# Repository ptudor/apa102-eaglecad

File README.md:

# apa102 controller

EAGLE schematic and board for apa102 controller

***
## the board

Top:

Bottom:

***

## the schematic

#### Power:

DC 5V, AMS1117-3V3, RT9193GB-33.

There is no onboard 5V voltage regulator. Power is supplied by an external switched power supply at 5V with a 2.1mm center positive jack, in a common wall-wart or laptop brick form factor. Two options are available for providing power: Space for a standard rectangular PCB-mount DC jack exists and optionally, to keep those milled slots clean, two holes labelled "red" and "black" are available for use with circular panel mount DC jacks. A fuse follows the voltage input connectors and a second fuse sits between the regular 5V on the PCB and the 5V supplied to the LED connector. Two big electrolytic capacitors sit after the 5V in and before the MCU side and LED side of the power to hopefully prevent brownouts if a strip suddenly changes from off to fully illuminated.

When connected to external USB, the 5V-USB, after a fuse, powers the onboard atmega88p USBASP and FT230X serial directly and runs to an AMS1117 3.3v voltage regulator that serves the USB Hub, CP2112 i2c, and the USB enable on the uBlox GPS. The 3V3 output has the datasheet suggested 22uF capacitor.

The uBlox GPS is powered by an RT9193 3.3v voltage regulator. The enable pin of this device is connected to the primary MCU on pin D4 so it can be turned off in software. Alternatively, a solder jumper permits connecting the pin directly to the primary 5V. The RT9193 has the datasheet recommended 22nF capacitor on the bypass pin for low-noise operation and the 3V3 output passes though a ferrite bead and tantalum capacitor on its way to the integrated circuit.

#### GPS:

A standard uBlox NEO 7M occupies the upper right quadrant of the board. The numerous vias and general layout are hopefully compliant with datasheet requirements. The PPS and TX pins connect to the MCU with RX left disconnected. There is board space for an external eeprom, a cheap and simple part, but it is generally not required.

A CR1220 battery is dedicated to the GPS to enable warm starts. An SMA connection reminds us an external active antenna is required. While the mini-USB connector is nearby, it is not directly connected to the GPS.

#### USB-i2c:

The bridge the gap between computers and the hardware on the circuit board, a CP2112 offers access to the i2c bus.

#### RTC:

Preserving time across reboots, an MCP79408 or MCP79412 is set and periodically synchronized by the GPS. To decouple GPS time and RTC time, the RTC has its own battery so that even if GPS precision is delayed because of a dead-battery cold start, hopefully the RTC has a good idea of at least what the current minute is.

#### MCU:

Basically equivalent in function to an Arduino Nano, the heart of the board is its ATMega328p. It controls the input and output and all those things.

The chip runs at 16MHz with an external crystal. The MOSI and SCK pins are protected with 220 Ohm PTC fuses and 5.1V Zener diodes in the style of Ruggeduino.

Refer to the example program for further details.

#### ISP:

For convenience, an onboard USBASP programmer exists. During assembly and initial configuration be mindful of the solder jumpers on the underside of the PCB connected to the RESET pin of the 6-pin IDC ISP header and the two pins that when jumpered allow USB power to flow to the atmega328p target.

#### USB Hub:

After the board added a fourth USB connector, it became time to just add a hub, the Texas Instruments TUSB2046B. 27 Ohm resistors should be present in the correct places and absent where appropriate. A 1.5k Ohm resistor is connected between USB-3V3 and the external D+ line to signal the device as high speed USB. There is a MAX809S attached on the reset pin to provide the necessary pulse at startup.

#### USB Serial:

A cheaper alternative to the common FT232RL at half the price this board has a FT230X for simple debugging with serial print statements from the MCU. All data pins other than Transmit-Out are disconnected.

#### Connections:

Header for LEDs. Batteries. ISP. USB.

#### Switch Debouncing:

normal hex inverter

#### Input:

ALPS trimpot, ALPS trimpot with switch

#### Temp Sensor:

MCP9808

***

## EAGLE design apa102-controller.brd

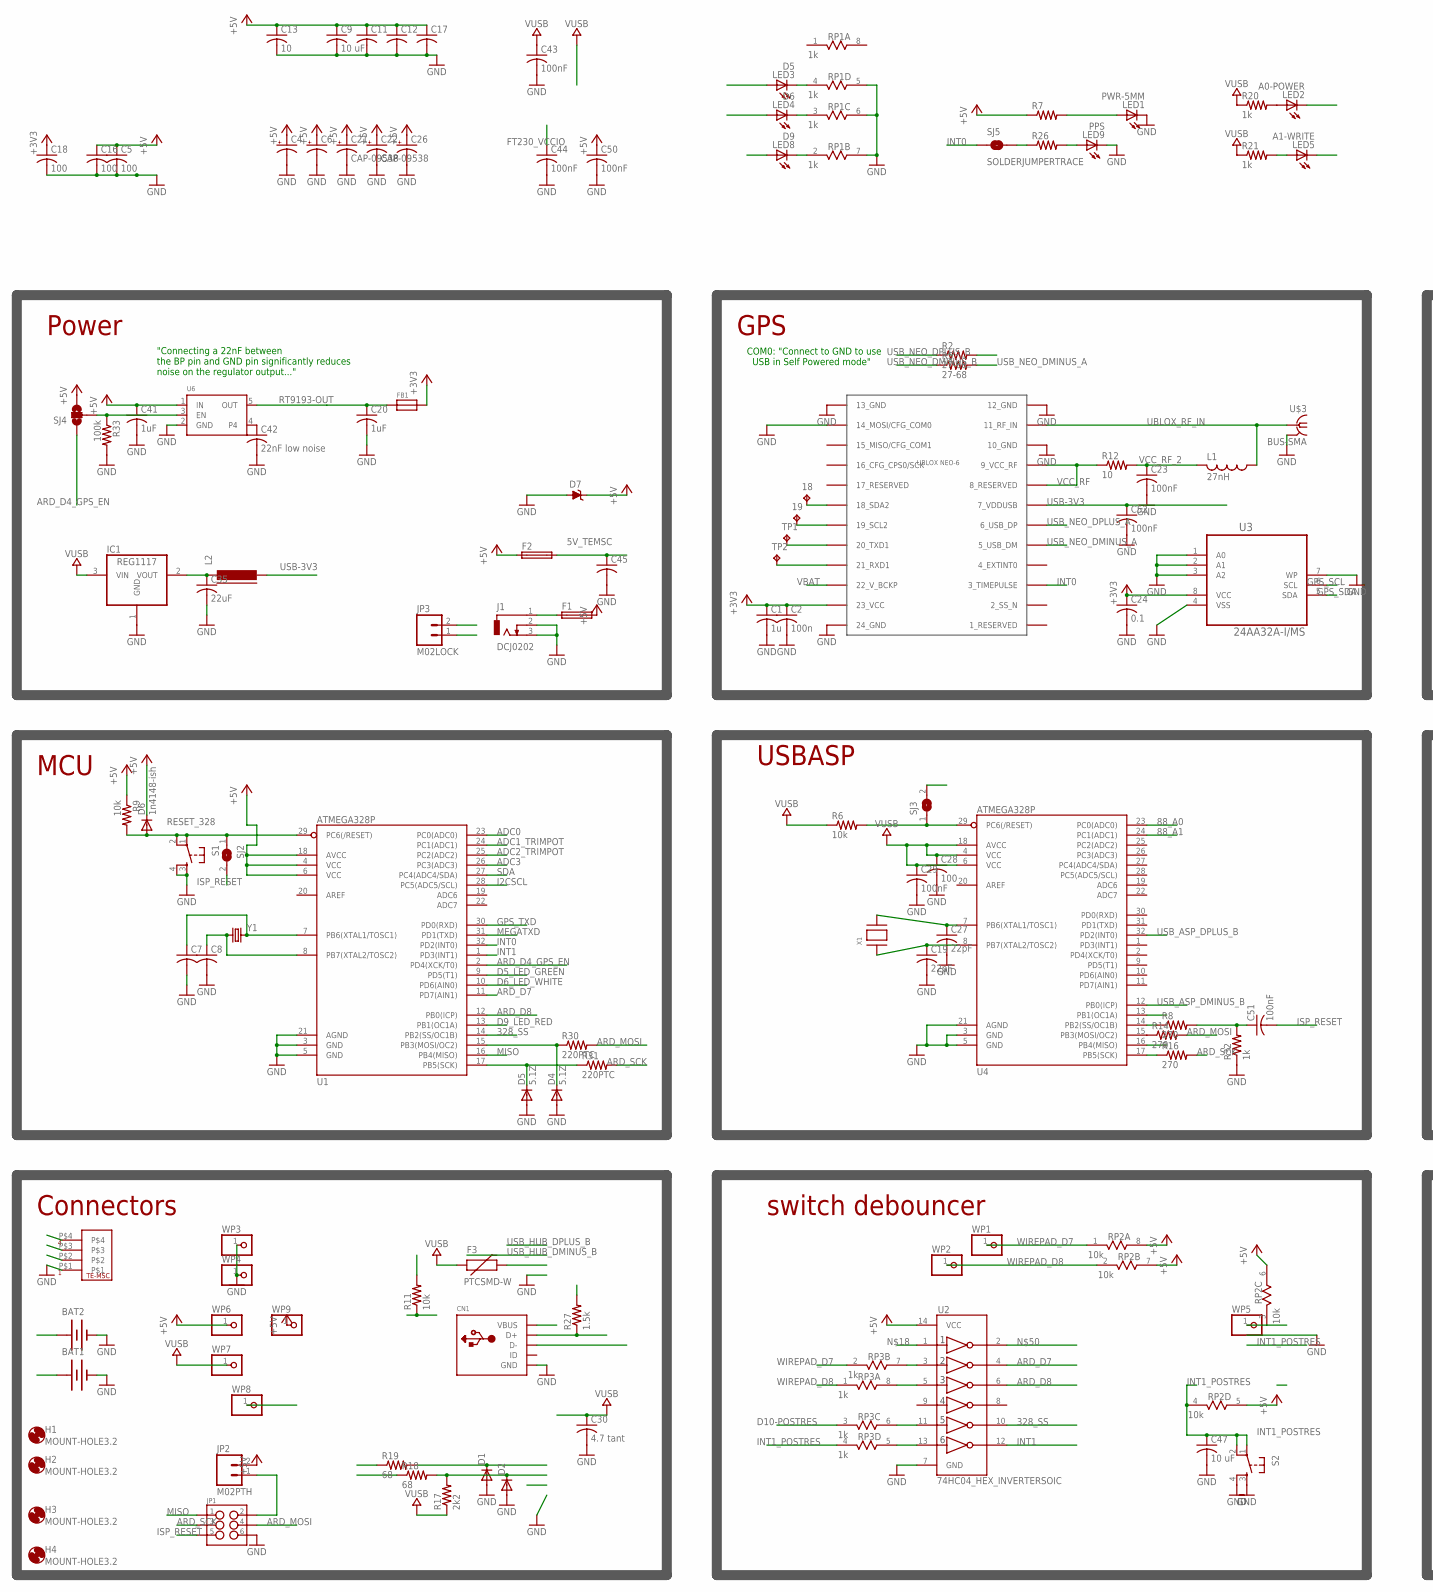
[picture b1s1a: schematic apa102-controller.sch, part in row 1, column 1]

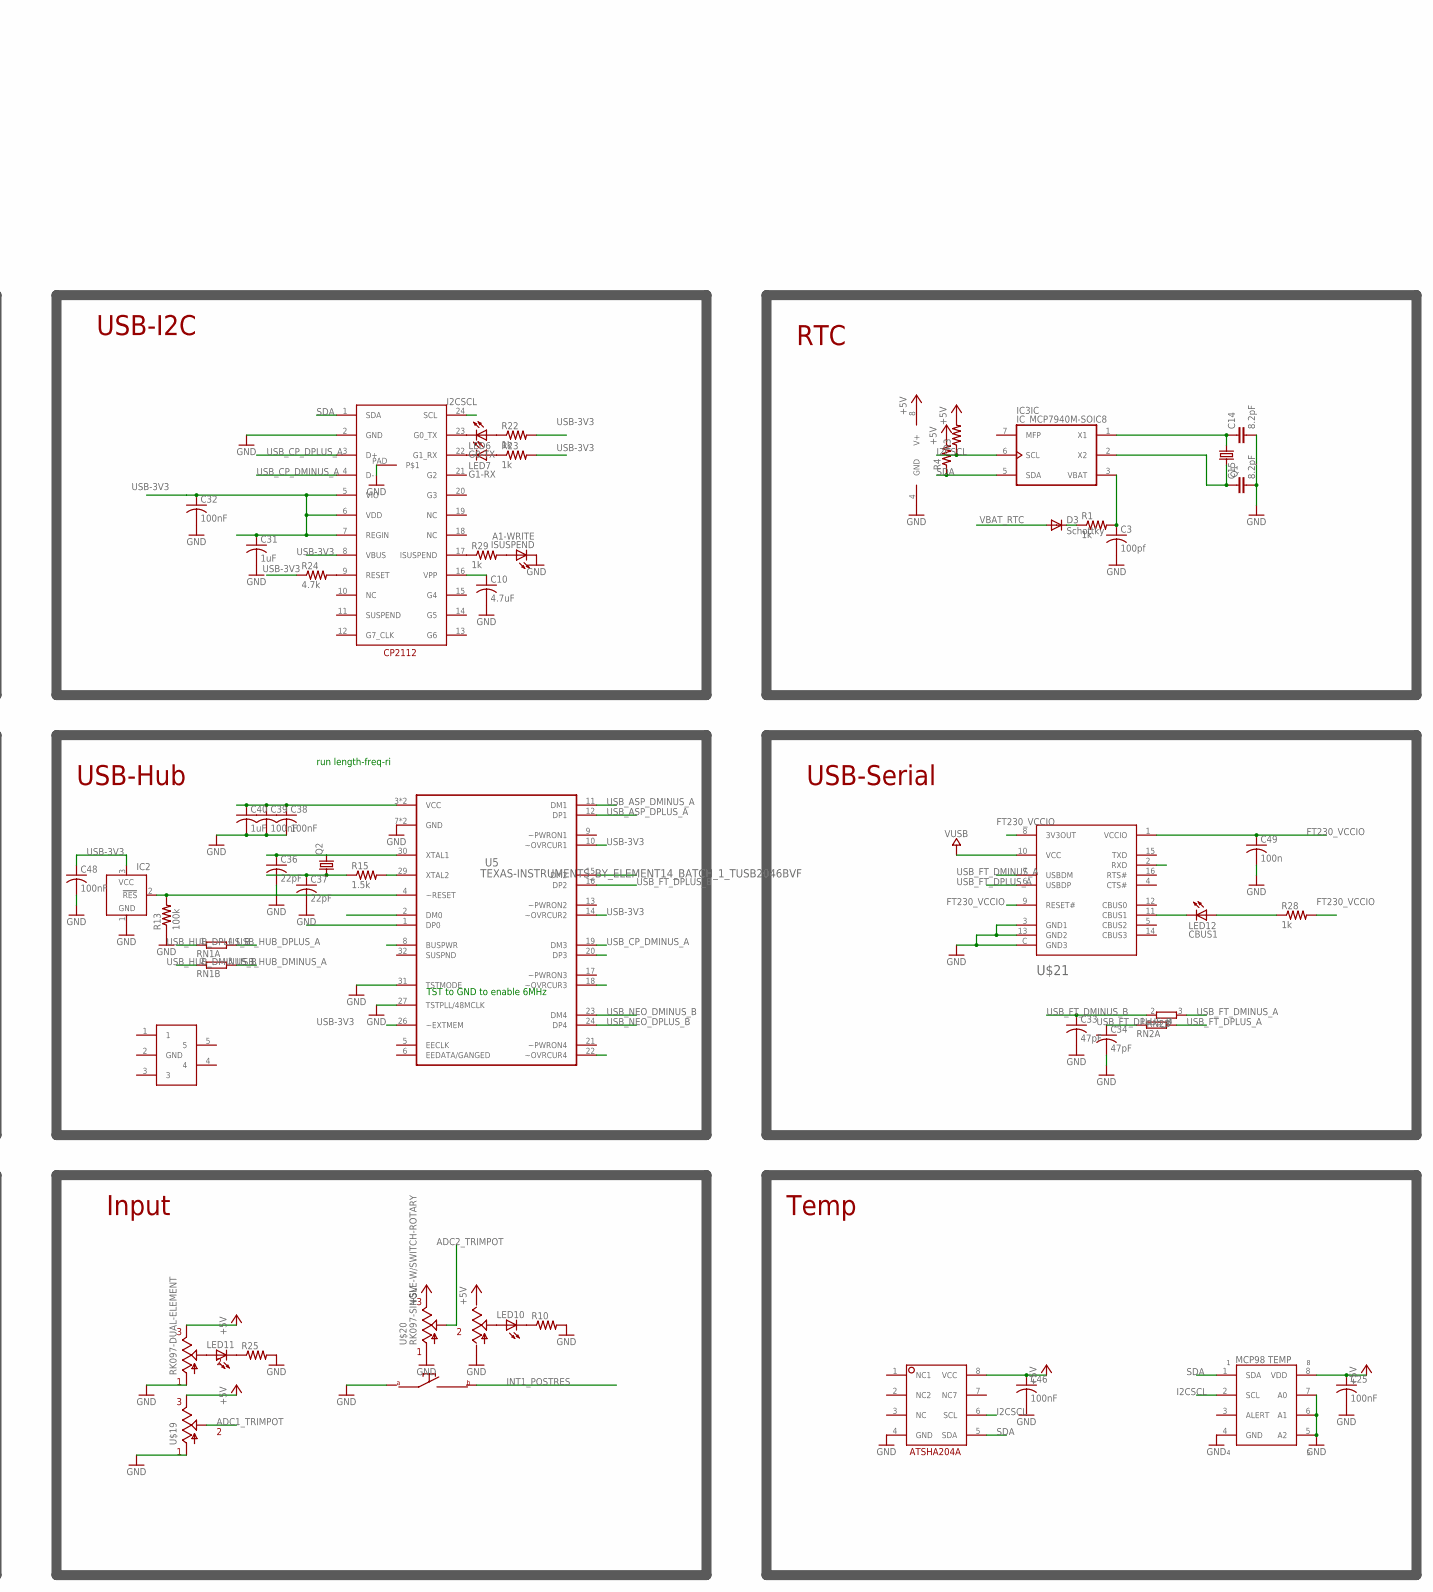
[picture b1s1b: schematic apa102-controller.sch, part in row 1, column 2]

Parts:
18, 19: TPTP10SQ; TP10SQ
BAT1, BAT2: BATTERY12MM; BATTCON_12MM
C1: 1u; C0805
C2, C49: 100n; C0805
C3: 100pf; C0805
C4, C6: CPOL-USE5-5; E5-5
C5, C16, C18, C28: 100; C0805
C7, C8, C11, C12, C17: C-USC0805; C0805
C9, C47: 10 uF; C0805
C10: 4.7uF; C0805
C13: 10; C0805
C14, C15: 8.2pF; 0603-CAP
C19, C27, C36, C37: 22pF; C0805
C20, C31, C40, C41: 1uF; C0805
C21, C22: CAP-09538; CPOL-RADIAL-1000UF-25V
C23, C25, C29, C32, C38, C39, C43, C44, C46, C48, C50, C51, C52: 100nF; C0805
C24: 0.1; C0805
C26: 10UF-25V-20%(PTH)KIT; CPOL-RADIAL-10UF-25V-KIT
C30: 4.7 tant; C0805
C33, C34: 47pF; C0805
C35: 22uF; C0805
C42: 22nF low noise; C0805
C45: C-USC1206K; C1206K
CN1: USBMINIB; USB-MINIB
D1, D2: DIODE-MINIMELF; MINIMELF@1
D3: Schottky; SOD323-W@1
D4, D5: 5.1Z; SOD323-W@1
D6: 1n4148-ish; SOD323-W@1
D7: ZENER-DIODEDO41Z10; DO41Z10
F1, F2: LITTLEFUSE
F3: PTCSMD-W; PTC-1206-WIDE
FB1: FERRITE0805; 0805
H1, H2, H3, H4: MOUNT-HOLE3.2; 3,2
IC1: REG1117; SOT223
IC2: TCM809; SOT23B-3
IC3: IC_MCP7940M-SOIC8; SOIC-8
ISUSPEND: A1-WRITE; CHIP-LED0805
J1: DCJ0202
JP1: M03X2SHROUD; 2X3-SHROUDED
JP2: M02PTH; 1X02
JP3: M02LOCK; 1X02_LOCK
L1: 27nH; M0805
L2: FERRITE-1206; FB1206
LED1: PWR-5MM; LED5MM
LED2: A0-POWER; CHIP-LED0805
LED3: D5; CHIP-LED0805
LED4: D6; CHIP-LED0805
LED5: A1-WRITE; CHIP-LED0805
LED6: G0-TX; CHIP-LED0805
LED7: G1-RX; CHIP-LED0805
LED8: D9; CHIP-LED0805
LED9: PPS; CHIP-LED0805
LED10, LED11: LEDCHIP-LED0805; CHIP-LED0805
LED12: CBUS1; CHIP-LED0805
Q1: CRYSTALMM20SS; MM20SS
Q2: CRYSTALHC49UP; HC49UP
R1, R20, R21, R22, R23, R28, R29, R32: 1k; R0805
R2, R5: 27-68; R0805
R3, R4, R7, R10, R25, R26: R-US_R0805; R0805
R6, R9, R11: 10k; R0805
R8, R14, R16: 270; R0805
R12: 10; R0805
R13, R33: 100k; R0805
R15, R27: 1.5k; R0805
R17: 2k2; R0805
R18, R19: 68; R0805
R24: 4.7k; R0805
R30, R31: 220PTC; 0603-RES
RN1, RN2: 2R-NEXBV4V; EXBV4V
RP1, RP3: 1k; RES4NT
RP2: 10k; RES4NT
S1, S2: TAC_SWITCHSMD; TACTILE-SWITCH-SMD
SJ2, SJ3: SJ
SJ4: SOLDERJUMPER_2WAYT; SJ_2
SJ5: SOLDERJUMPERTRACE; SJ_2S-TRACE
TP1, TP2: TPTP10SQ; TP10SQ
U1, U4: ATMEGA328P; TQFP32-08
U2: 74HC04_HEX_INVERTERSOIC; SOIC-14
U3: 24AA32A-I/MS; SOP65P490X110-8N
U5: TEXAS-INSTRUMENTS_BY_ELEMENT14_BATCH_1_TUSB2046BVF; TEXAS-INSTRUMENTS_BY_ELEMENT14_BATCH_1_QFP80P900X900X145-32N
U6: VREG_SOT23-5; SOT23-5
U$2: UBLOX_NEO-6; UBLOX_NEO-6P
U$3: BUS-SMA
U$7: MCP98; MSOP08
U$11: CP2112; QFN-24
U$17: TE-MSC-4POS-6A
U$18: ATSHA204A; SO08
U$19: RK097-DUAL-ELEMENT
U$20: RK097-SINGLE-W/SWITCH-ROTARY; RK097-DUAL-ELEMENT-W/SWITCH
U$21: FT230XQ; QFN4X4-16
U$23: ESDTUDOR; SOT23-5L
WP1, WP2, WP3, WP4, WP5, WP6, WP7, WP8, WP9: WPAD-1-PTH; WPAD-1-PTH-2.54
X1: XTALNX5032; NX5032
Y1: CRYSTALABM2; CRYSTAL-ABRACON-ABM2

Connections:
5V_TEMSC: C45.1, F2.2, U$17.P$4
88_A0: LED2.C, U4.23 (PC0(ADC0))
88_A1: LED5.C, U4.24 (PC1(ADC1))
328_SS: U1.14 (PB2(SS/OC1B)), U2.10 (5Y)
+3V3: C1.1, C2.1, C18.1, C24.1, FB1.2, U3.8 (VCC), U$2.23_VCC
+5V: C4.+, C5.1, C6.+, C9.1, C11.1, C12.1, C13.1, C16.1, C17.1, C21.+, C22.+, C25.1, C26.1 (+), C41.1, C46.1, C50.1, D6.C, D7.C, F1.2, F2.1, IC3.8 (V+), JP2.2, R3.2, R4.2, R7.1, R9.1, RP2.5 (2), RP2.6 (2), RP2.7 (2), RP2.8 (2), SJ4.3, U1.4 (VCC), U1.6 (VCC), U1.18 (AVCC), U2.14 (VCC), U6.1 (IN), U$7.8 (VDD), U$18.8 (VCC), U$19.P$3 (E1), U$19.P$6 (E), U$20.P$3 (E), U$20.P$6 (E1), WP6.1, WP9.1
ADC0: U1.23 (PC0(ADC0))
ADC1_TRIMPOT: U1.24 (PC1(ADC1)), U$19.P$5 (S1)
ADC2_TRIMPOT: U1.25 (PC2(ADC2)), U$20.P$2 (S)
ADC3: U1.26 (PC3(ADC3))
ARD_D4_GPS_EN: R33.1, SJ4.1, SJ4.2, U1.2 (PD4(XCK/T0)), U6.3 (EN)
ARD_D7: U1.11 (PD7(AIN1)), U2.4 (2Y)
ARD_D8: U1.12 (PB0(ICP)), U2.6 (3Y)
ARD_MOSI: JP1.4, R14.2, R30.2, U$17.P$2
ARD_SCK: JP1.3, R16.2, R31.2, U$17.P$3
D5_LED_GREEN: LED3.A, U1.9 (PD5(T1))
D6_LED_WHITE: LED4.A, U1.10 (PD6(AIN0))
D9_LED_RED: LED8.A, U1.13 (PB1(OC1A))
D10-POSTRES: RP2.3 (1), RP3.3 (1), WP5.1
DCJACK_TO_PTC: F1.1, J1.1, JP3.1
FT230_VCCIO: C44.1, C49.1, R11.2, R28.2, U$21.1 (VCCIO), U$21.8 (3V3OUT), U$21.9 (RESET#)
FT_CB0: LED12.C, U$21.11 (CBUS1)
GND: BAT1.GND (-), BAT2.GND (-), C1.2, C2.2, C3.2, C4.-, C5.2, C6.-, C7.2, C8.2, C9.2, C10.2, C11.2, C12.2, C13.2, C14.2, C15.2, C16.2, C17.2, C18.2, C19.2, C20.2, C21.-, C22.-, C23.2, C24.2, C25.2, C26.2 (-), C27.2, C28.2, C29.2, C30.2, C31.2, C32.2, C33.2, C34.2, C35.2, C36.2, C37.2, C38.2, C39.2, C40.2, C41.2, C42.2, C43.2, C44.2, C45.2, C46.2, C47.2, C48.2, C49.2, C50.2, C52.2, CN1.GND, D1.A, D2.A, D4.A, D5.A, D7.A, IC1.1 (GND), IC2.1 (GND), IC3.4 (GND), ISUSPEND.C, J1.2, J1.3, JP1.6, JP3.2, LED1.K (C), LED9.C, R10.2, R13.1, R25.2, R32.1, R33.2, RP1.5 (2), RP1.6 (2), RP1.7 (2), S1.3, S1.4, S2.3, S2.4, U1.3 (GND), U1.5 (GND), U1.21 (AGND), U2.7 (GND), U3.1 (A0), U3.2 (A1), U3.3 (A2), U3.4 (VSS), U3.7 (WP), U4.3 (GND), U4.5 (GND), U4.21 (AGND), U5.7 (GND), U5.27 (TSTPLL/48MCLK), U5.28 (GND), U5.31 (TSTMODE), U6.2 (GND), U$2.10_GND, U$2.12_GND, U$2.13_GND, U$2.14_MOSI/CFG_COM0, U$2.24_GND, U$3.2 (GND), U$3.3 (GND), U$3.4 (GND), U$3.5 (GND), U$7.4 (GND), U$7.5 (A2), U$7.6 (A1), U$7.7 (A0), U$11.2 (GND), U$11.PAD, U$17.P$1, U$18.4 (GND), U$19.P$1 (A1), U$19.P$4 (A), U$20.P$1 (A), U$20.P$4 (A1), U$20.P$7 (SW1), U$21.3 (GND1), U$21.13 (GND2), U$21.C (GND3), WP3.1, WP4.1
GPS_RXD: TP2.TP, U$2.21_RXD1
GPS_SCL: 19.TP, U3.6 (SCL), U$2.19_SCL2
GPS_SDA: 18.TP, U3.5 (SDA), U$2.18_SDA2
GPS_TXD: TP1.TP, U1.30 (PD0(RXD)), U$2.20_TXD1
HEX3: RP3.7 (2), U2.3 (2A)
HEX5: RP3.8 (2), U2.5 (3A)
HEX11: RP3.6 (2), U2.11 (5A)
HEX13: RP3.5 (2), U2.13 (6A)
I2CSCL: IC3.6 (SCL), R3.1, U1.28 (PC5(ADC5/SCL)), U$7.2 (SCL), U$11.24 (SCL), U$18.6 (SCL)
INT0: SJ5.1, U1.32 (PD2(INT0)), U$2.3_TIMEPULSE
INT1: U1.1 (PD3(INT1)), U2.12 (6Y)
INT1_POSTRES: C47.1, RP2.4 (1), RP3.4 (1), S2.1, S2.2, U$20.P$8 (SW2)
ISP_RESET: C51.2, JP1.5, SJ2.2, SJ3.2
MEGATXD: R11.1, U1.31 (PD1(TXD)), U$21.2 (RXD)
MISO: JP1.1, U1.16 (PB4(MISO)), U4.16 (PB4(MISO))
unnamed: C3.1, IC3.3 (VBAT), R1.2
unnamed: D3.C, R1.1
unnamed: C35.1, IC1.2 (VOUT), L2.1
unnamed: LED10.A, U$20.P$5 (S1)
unnamed: C42.1, U6.4
unnamed: LED1.A, R7.2
unnamed: D4.C, R30.1, U1.15 (PB3(MOSI/OC2))
unnamed: IC2.2 (!RES), R13.2, U5.4 (~RESET)
unnamed: C7.1, U1.7 (PB6(XTAL1/TOSC1)), Y1.P$2 (2)
unnamed: C8.1, U1.8 (PB7(XTAL2/TOSC2)), Y1.P$1 (1)
unnamed: C14.1, IC3.1 (X1), Q1.1
unnamed: C15.1, IC3.2 (X2), Q1.4 (2)
unnamed: LED3.C, RP1.4 (1)
unnamed: LED4.C, RP1.3 (1)
unnamed: LED10.C, R10.1
unnamed: R15.2, U5.29 (XTAL2)
unnamed: LED11.A, U$19.P$2 (S)
unnamed: LED11.C, R25.1
unnamed: LED6.C, U$11.23 (G0_TX)
unnamed: LED7.C, U$11.22 (G1_RX)
unnamed: R6.2, SJ3.1, U4.29 (PC6(/RESET))
unnamed: C19.1, U4.8 (PB7(XTAL2/TOSC2)), X1.P$1
unnamed: C27.1, U4.7 (PB6(XTAL1/TOSC1)), X1.P$2
unnamed: R8.1, U4.14 (PB2(SS/OC1B))
unnamed: R14.1, U4.15 (PB3(MOSI/OC2))
unnamed: R16.1, U4.17 (PB5(SCK))
unnamed: C36.1, Q2.2, U5.30 (XTAL1)
unnamed: C37.1, Q2.1, R15.1
unnamed: JP1.2, JP2.1
unnamed: LED2.A, R20.2
unnamed: LED5.A, R21.2
unnamed: LED6.A, R22.1
unnamed: LED7.A, R23.1
unnamed: R24.2, U$11.9 (RESET)
unnamed: C10.1, U$11.16 (VPP)
unnamed: R29.1, U$11.17 (ISUSPEND)
unnamed: LED8.C, RP1.2 (1)
unnamed: ISUSPEND.A, R29.2
unnamed: D5.C, R31.1, U1.17 (PB5(SCK))
unnamed: LED9.A, R26.2
unnamed: R26.1, SJ5.2
unnamed: C51.1, R8.2, R32.2
unnamed: LED12.A, R28.1
RESET_328: D6.A, R9.2, S1.1, S1.2, SJ2.1, U1.29 (PC6(/RESET))
RT9193-OUT: C20.1, FB1.1, U6.5 (OUT)
SDA: IC3.5 (SDA), R4.1, U1.27 (PC4(ADC4/SDA)), U$7.1 (SDA), U$11.1 (SDA), U$18.5 (SDA)
UBLOX_RF_IN: L1.1, U$2.11_RF_IN, U$3.1
USB-3V3: C31.1, C32.1, C38.1, C39.1, C40.1, C48.1, C52.1, IC2.3 (VCC), L2.2, R22.2, R23.2, R24.1, R27.2, U5.3 (VCC), U5.8 (BUSPWR), U5.10 (~OVRCUR1), U5.14 (~OVRCUR2), U5.18 (~OVRCUR3), U5.22 (~OVRCUR4), U5.25 (VCC), U5.26 (~EXTMEM), U$2.7_VDDUSB, U$11.5 (VIO), U$11.6 (VDD), U$11.7 (REGIN), U$11.8 (VBUS), WP8.1
USB_ASP_DMINUS_A: D2.C, R17.2, R18.2, U5.11 (DM1)
USB_ASP_DMINUS_B: R18.1, U4.12 (PB0(ICP))
USB_ASP_DPLUS_A: D1.C, R19.2, U5.12 (DP1)
USB_ASP_DPLUS_B: R19.1, U4.13 (PB1(OC1A)), U4.32 (PD2(INT0))
USB_CP_DMINUS_A: U5.19 (DM3), U$11.4 (D-)
USB_CP_DPLUS_A: U5.20 (DP3), U$11.3 (D+)
USB_FT_DMINUS_A: RN2.3 (2), U$21.7 (USBDM)
USB_FT_DMINUS_B: C33.1, RN2.2 (1), U5.15 (DM2)
USB_FT_DPLUS_A: RN2.4 (2), U$21.6 (USBDP)
USB_FT_DPLUS_B: C34.1, RN2.1, U5.16 (DP2)
USB_HUB_DMINUS_A: RN1.3 (2), U5.2 (DM0)
USB_HUB_DMINUS_B: CN1.D-, RN1.2 (1)
USB_HUB_DPLUS_A: RN1.4 (2), U5.1 (DP0)
USB_HUB_DPLUS_B: CN1.D+, R27.1, RN1.1
USB_NEO_DMINUS_A: R5.2, U$2.5_USB_DM
USB_NEO_DMINUS_B: R5.1, U5.23 (DM4)
USB_NEO_DPLUS_A: R2.2, U$2.6_USB_DP
USB_NEO_DPLUS_B: R2.1, U5.24 (DP4)
USB_RAW_5V: CN1.VBUS, F3.2
VBAT: BAT1.PWR@1 (+), U$2.22_V_BCKP
VBAT_RTC: BAT2.PWR@1 (+), D3.A
VCC_RF: R12.1, U$2.8_RESERVED, U$2.9_VCC_RF
VCC_RF_2: C23.1, L1.2, R12.2
VUSB: C28.1, C29.1, C30.1, C43.1, F3.1, IC1.3 (VIN), R6.1, R17.1, R20.1, R21.1, U4.4 (VCC), U4.6 (VCC), U4.18 (AVCC), U$21.10 (VCC), WP7.1
WIREPAD_D7: RP2.1, RP3.2 (1), WP1.1
WIREPAD_D8: RP2.2 (1), RP3.1, WP2.1

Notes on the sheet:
COM0: "Connect to GND to use USB in Self Powered mode"
TST to GND to enable 6MHz
Connectors
Power
Input
MCU
USB-Serial
USB-Hub
USB-I2C
GPS
RTC
Temp
USBASP
switch debouncer
"Connecting a 22nF between the BP pin and GND pin significantly reduces noise on the regulator output..."
run length-freq-ri

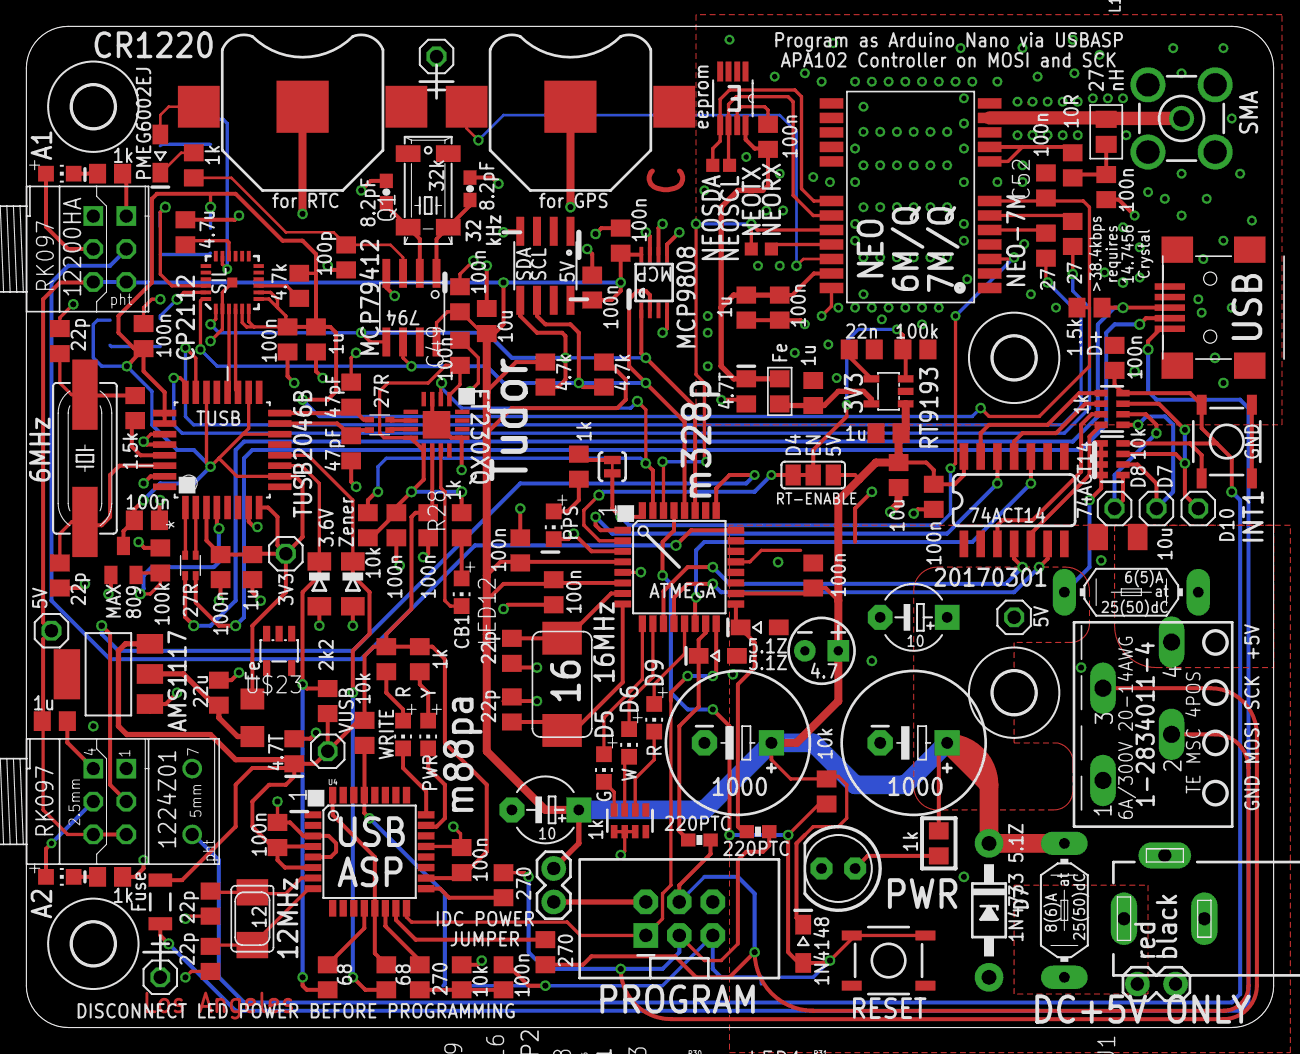
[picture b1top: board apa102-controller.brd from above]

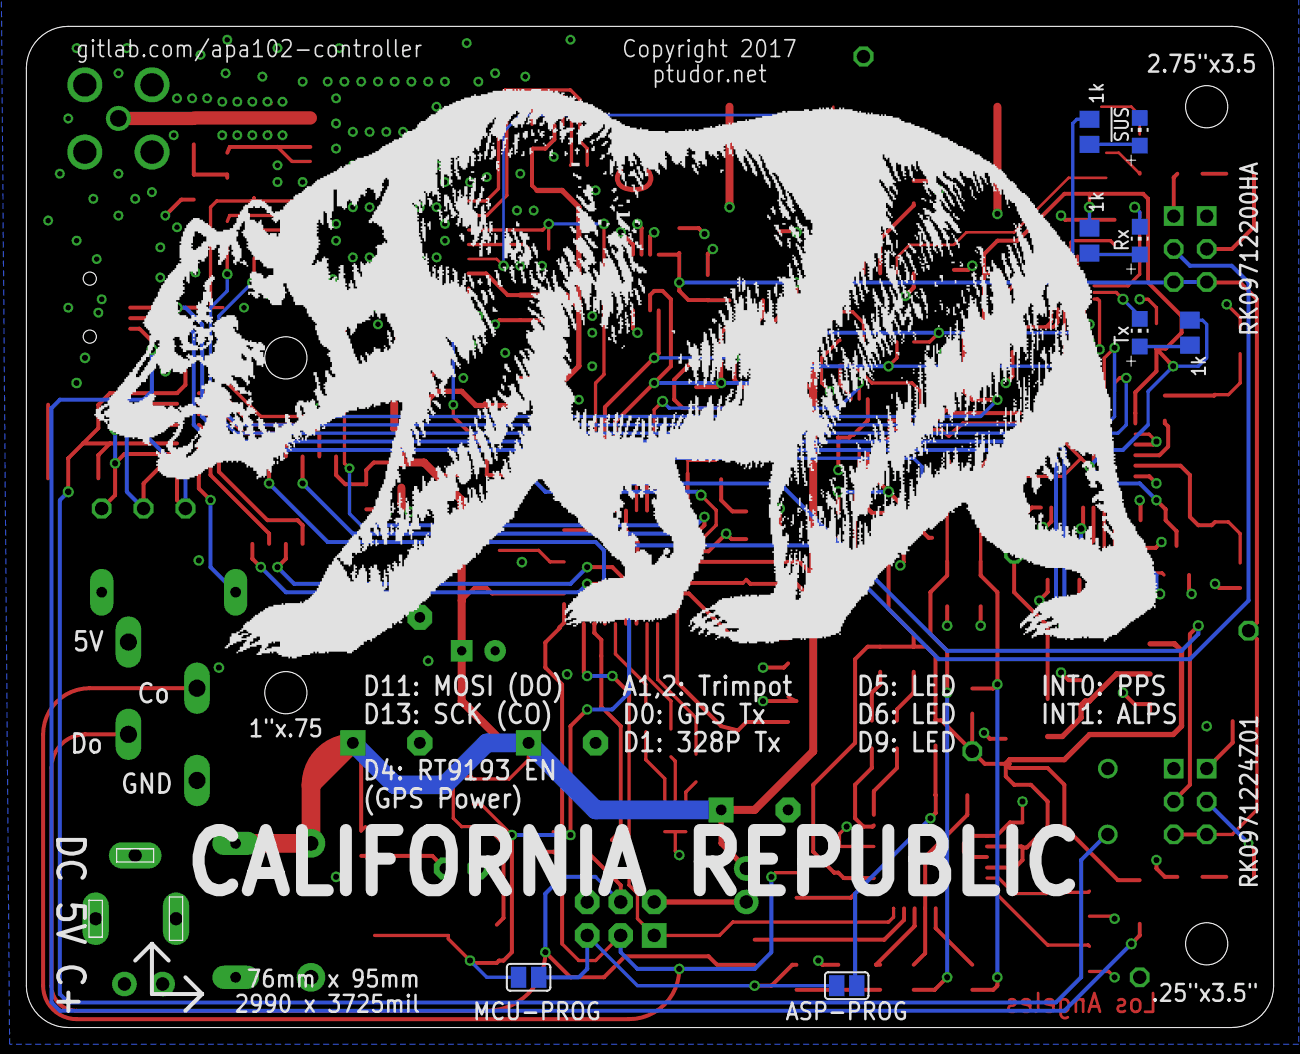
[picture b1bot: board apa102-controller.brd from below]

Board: 2 copper layers, 94.6 x 75.9 mm, 170 parts (9 on the bottom side), 110 nets.

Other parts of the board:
U$1: BEARMED200DPI

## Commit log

2017-02-03 git add LICENSE
2017-02-05 more labels
2017-02-09 pcbs 20170206
2017-02-25 add 1N4733 Zener
2017-02-27 labels
2017-02-27 git add GITHUB.md
2020-11-21 git commit gerblook.org README.md
2020-11-21 add png
2020-11-21 experiment
2020-11-21 prefer png in-browser

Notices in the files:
apa102-controller.brd:
Copyright 2017
parts and their libraries:
SparkFun-Connectors: Licensing: Creative Commons ShareAlike 4.0 International - https://creativecommons.org/licenses/by-sa/4.0
PatternAgents-ProtoPads: License : http://creativecommons.org/licenses/by-sa/4.0
(Creative Commons 4.0)
